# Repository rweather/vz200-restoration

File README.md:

VZ200 Restoration
=================

This repository chronicles my exploits in restoring a Dick Smith VZ200
that I got off eBay.  The VZ200 is a rebadged VTech Laser 200, which was
sold in Australia from 1983 onwards.

The eBay seller Ben had this to say about the unit: "It was an op-shop
pickup from my Nan and had been in storage in a plastic container for who
knows how long.  As it did not have any leads I never tested it."

## Technical specifications

* Z80A 8-bit CPU, running at 3.58MHz.
* 16K of ROM containing BASIC.
* 2K of video RAM for either 32 x 16 text mode or 128 x 64 graphics mode.
* 6K of user program RAM, expandable to 22K using a 16K RAM expansion module.
* 45 key chiclet keyboard organized in a 6x8 matrix.
* Motorola 6847 video processor.
* RF and composite video output.

Note: The VZ300 is essentially the same computer except that it has 16K of
user program RAM on-board and a mechanical keyboard.

Outside of Australia and New Zealand, the VZ200 and VZ300 were known as the
Laser 200 and Laser 310 respectively.

## Updates

Since doing the original restoration, I was gifted some more VZ200/VZ300
gear from a friend at work, Brian.  Brian got these years ago from an old
fellow in the local amateur radio network who was obviously a big fan of the
VZ computers, but was getting too old to work on them.

Many of the pieces have custom modifications and may or may not work.
Brian had 2 or 3 of everything.  He gave me these and kept the rest:

* Set of joysticks (working, just needed a clean).
* Printer interface.
* [16K memory expansion module that has been modified to 32K](Memory_Expansion_32K.md)
* Data casette recorder.
* Floppy disk controller and floppy disk drive.  Plus some floppy disks.
  Drive almost works but has a head crash; needs head re-alignment.
* Serial port kit.
* [Two VZ300's that were not working, but one now is.](VZ300_Restoration.md)

The links point at information about the restoration on each item.

Brian also gifted me a Microbee kit (assembled), two TRS-80 color computers,
and a TRS-80 printer/plotter.

I will gradually work on restoring these and post the results as I go.

And now onto the original restoration ...

## Restoration

Note: All images below have been scaled down.  Use "Open Image in New Tab"
or equivalent in your Web browser for a full-sized image.

### Initial condition of the unit

There were no power or video cables with the unit that was shipped to me.
The unit had not been powered on for a long time.  The power input is 9V DC
with a standard DC barrel jack, so power can be easily supplied with a
modern plugpack / wall wart.

The outside of the case was dirty, but nothing that some water, Windex,
paper towels, and elbow grease wouldn't fix.  The plastic was a little
yellowed but not too bad.

Serial number 075172.

The covers for the memory expansion and peripheral ports were still in place,
so I was hopeful that it had never been opened.

However, once inside I discovered some dirt and the braids connecting the
RF shield to ground had been cut:

It looks like someone had tried to remove the RF shield before and had
not succeeded.  The shield is soldered down to the motherboard, but some
of the legs were loose indicating partial success.

### Checking rail-to-rail resistance

I measured the resistance between 5V and ground - 284 ohms.  The same
between 9V and ground.  Probably OK.  Not a dead short anyway.

The resistance between 5V and 9V was 34 ohms, due to an actual 32 ohm
resistor between the two:

### Removing the keyboard

I had to remove the keyboard from the top half of the case to clean the
case properly.  It looks like the original keyboard was in a module that
was pushed in from the top and then snapped into place.  Removing the
screws was easy, but I couldn't slide out the keyboard PCB without
cutting the snaps or the cross-piece.  I elected to cut the cross-piece:

The keyboard PCB has scratched-on letters indicating which key is which.
That's useful.

After that, it was easy to remove the rubber membrane for cleaning.
The key caps themselves are molded into the membrane, so there are no
individual keys to get lost.  The membrane was filthy:

### Removing the RF shield

The person who tried to remove the RF shield didn't do a very good job.
Solder had bridged tracks, and one of the tracks was ripped right off the PCB:

Using a solder sucker, solder wick, flux, heat, and some patience,
I managed to clean up the excess solder and get the shield off:

Here is the same photo with the major components marked up:

And here is a diagram that shows the location of all IC's, looking forward
from the front of the PCB (not to scale):

### Cleaning the case and keyboard membrane

I cleaned the top and bottom of the case and the keyboard membrane
with Windex and water.  Some stubborn stains on the back were cleaned
off with isopropyl alchohol.

### First power on test

I connected a current-limited bench power supply set to 9V and 1A and
gingerly turned it on.  The 7805 voltage regulator was putting out 4.925V
and the system was consuming 650mA from the 9V supply.  So it looks like
no dead shorts on the board.

No blue smoke escaped, and the power LED turned on, so that's good.

### Checking signals

I checked the signals coming out of the CPU.  The clock on pin 6
was sitting at 3.57797MHz - close enough to 3.58MHz.

The address lines and most data lines had reasonable looking activity,
but D1, D2, and D6 had weird-looking signals like this for D6:

The base line of the signal is shifted up by about 1.7V.  D1 and D2 were
also shifted to half-way between 0V and 5V.  So there was a conflict
on the data bus somewhere.

### Video test

Connecting up a Composite-to-HDMI video converter, I got garbage on
the screen.  Powering on and off multiple times gives different garbage
each time:

The video clock into the MC6847 was around 3MHz, the "HS" horizontal sync
signal out was around 13kHz, and the "FS" frame sync signal out was 50Hz.

The video clock should be 3.58MHz.  However, the schematic gates the
main 3.58MHz system clock to generate the video clock.  "CLK" is the
main system clock:

In some parts of the frame during the horizontal and vertical sync times,
the video clock is disabled.  I think my oscilloscope was getting confused
and showing the average clock rate which undercounts due to the gating.
The same applies to the horizontal sync signal which isn't active for the
entire frame.

The frame sync was bang on 50Hz, and the generated video looked reasonable,
so the MC6847 must be getting the right timing.

The pictures don't show it, but there was a lot of static on the screen
which may be due to the clock signals, the CPU struggling to write to
video RAM, or a noisy component in the video output circuitry.

### Replacing the ROM's

From information I gleaned online, a common cause of bus crashes on the
VZ200 are the 2364 mask ROM's U9 and U10.  In [this video](https://www.youtube.com/watch?v=YIOjtE3j2aw)
from Tommy Ovesen at [Arctic Retro](https://www.arcticretro.com/),
he had similar screen corruption to my case.

Tommy replaced almost all the chips on the board before replacing the ROM's.
The ROM's were the ultimate culprit.  Rather than try replacing bus
transceivers, the CPU, or the video chip, I decided to learn from Tommy's
excellent work and start with the ROM's.

The wrinkle is that the original ROM's are 24-pin 2364's, but the best
replacements would be 28-pin 2764 EPROM's or (even better) AT28C64 EEPROM's.

It turns out that the PCB actually prefers 28-pin EPROM's!  There are
extra pin holes for the 28-pin footprint:

And on the back there are bodge wires to remap the 28-pin footprint into
24-pin so that the 2364's can be fitted:

If we look at the original schematic in the
[VZ200 Technical Reference Manual](http://www.vz200.org/bushy/VZ200_technical_reference_manual.pdf), we can see that the footprint was supposed to be 28-pin:

My guess is that the manufacturer originally intended to use 28-pin
2764 EPROM's, but to save cost they went with 24-pin 2364's instead.
Apparently it was cheaper to pay people to modify thousands of PCB's
with bodge wires than to re-spin the PCB.

This was good for me.  I removed the ROM's and the bodge wires, and then
re-bodged the PCB back to the 28-pin footprint for the two AT28C64B-15PU
EEPROM's that I purchased from Mouser.  The following table shows the pin
mapping between the 24-pin and 28-pin footprints, with the major changes
shown in bold:

<table border="1">
<tr><td><b>2364 Pin</b></td><td><b>Connection</b></td><td><b>AT28C64 Pin</b></td><td><b>Connection</b></td></tr>
<tr><td> </td><td> </td><td><b>1</b></td><td><b>5V</b></td></tr>
<tr><td> </td><td> </td><td><b>2</b></td><td><b>A12</b></td></tr>
<tr><td>1</td><td>A7</td><td>3</td><td>A7</td></tr>
<tr><td>2</td><td>A6</td><td>4</td><td>A6</td></tr>
<tr><td>3</td><td>A5</td><td>5</td><td>A5</td></tr>
<tr><td>4</td><td>A4</td><td>6</td><td>A4</td></tr>
<tr><td>5</td><td>A3</td><td>7</td><td>A3</td></tr>
<tr><td>6</td><td>A2</td><td>8</td><td>A2</td></tr>
<tr><td>7</td><td>A1</td><td>9</td><td>A1</td></tr>
<tr><td>8</td><td>A0</td><td>10</td><td>A0</td></tr>
<tr><td>9</td><td>D0</td><td>11</td><td>D0</td></tr>
<tr><td>10</td><td>D1</td><td>12</td><td>D1</td></tr>
<tr><td>11</td><td>D2</td><td>13</td><td>D2</td></tr>
<tr><td>12</td><td>GND</td><td>14</td><td>GND</td></tr>
<tr><td>13</td><td>D3</td><td>15</td><td>D3</td></tr>
<tr><td>14</td><td>D4</td><td>16</td><td>D4</td></tr>
<tr><td>15</td><td>D5</td><td>17</td><td>D5</td></tr>
<tr><td>16</td><td>D6</td><td>18</td><td>D6</td></tr>
<tr><td>17</td><td>D7</td><td>19</td><td>D7</td></tr>
<tr><td><b>18</b></td><td><b>A11</b></td><td><b>20</b></td><td><b>CE</b></td></tr>
<tr><td>19</td><td>A10</td><td>21</td><td>A10</td></tr>
<tr><td><b>20</b></td><td><b>CE</b></td><td><b>22</b></td><td><b>RD</b></td></tr>
<tr><td><b>21</b></td><td><b>A12</b></td><td><b>23</b></td><td><b>A11</b></td></tr>
<tr><td>22</td><td>A9</td><td>24</td><td>A9</td></tr>
<tr><td>23</td><td>A8</td><td>25</td><td>A8</td></tr>
<tr><td>24</td><td>5V</td><td>26</td><td>5V</td></tr>
<tr><td> </td><td> </td><td><b>27</b></td><td><b>5V</b></td></tr>
<tr><td> </td><td> </td><td><b>28</b></td><td><b>5V</b></td></tr>
</table>

<b>Note:</b> The chip enable "CE" pins for the two ROM's are connected
to different pins on U3 / 74LS139.  CE on U9 / ROM0 should be connected
to pin 4 on U3.  CE on U10 / ROM1 should be connected to pin 5 on U3.
All other pins are connected identically on both ROM's.

Here is the PCB with the new ROM's fitted:

And here are the bodge wires I added on the back of the PCB:

During the ROM removal process, I ripped up a few of the tracks so I have a
few more bodge wires than would be strictly necessary for the bold
alterations listed above.  Not my finest soldering job, but servicable.

The ROM images are available from Bushy's website.  Download the
"Everything" bundle from [here](http://www.vz200.org/bushy/software.html).
The ROM images are under "`ROMs/VZ ROM`" in the ZIP archive.  I used the files
`vtechv20.u09` and `vtechv20.u10`.

I used a TL866II Plus EEPROM Programmer and [minipro](https://gitlab.com/DavidGriffith/minipro) to flash the AT28C64B-15PU chips:

    <Put the first EEPROM in the programmer's socket>
    minipro -p AT28C64B -w vtechv20.u09

    <Put the second EEPROM in the programmer's socket>
    minipro -p AT28C64B -w vtechv20.u10

It is important to use the device name "AT28C64B" instead of "AT28C64"
with minipro.  The device name without the "B" didn't work.

With the 28-pin modifications above, it should be possible to fit
AT28C128 (16K) or AT28C256 (32K) instead of AT28C64 (8K).
The high address lines will be pulled high, so you will need to
flash the images into the top-most 8K of the replacement EEPROM's.
You will still need two EEPROM's, even if they are 16K or 32K in size,
because of how address decoding works on the PCB.

### Testing

After replacing the ROM's, I hooked up the power and composite video output
and turned the computer on.  This happened:

Yay!  It works!  The text is correct, the cursor blinks, and there is no
static on the screen.  So replacing the ROM's did the trick.

The current draw of the unit was originally 650mA on the 9V input.
After replacing the ROM's, the current draw is now 550mA.

### Keyboard ribbon cable

After repeated handling of the PCB while replacing the ROM's, the soldered-on
keyboard ribbon cable eventually tore off the PCB.  So I replaced it with a
proper connector setup using 2.54mm pin headers and sockets:

There is more than enough room in the case for the connector, so there
weren't any clearance issues:

After connecting the keyboard, I tried writing a little BASIC program:

All of the keys work reliably except CTRL.  Sometimes it works, but not always.
May be an alignment issue or something wrong with the membrane under the key.

### Fixing the CTRL key

I disassembled the keyboard again and carefully scrubbed the contacts on the
PCB and the membrane itself with dry cotton buds.  There was still a little
dirt in the membrane and on the contacts.

Previously I tightened the keyboard screws quite tight when I reassembled
the keyboard.  One theory I had was that the membrane didn't have enough
"play" because it was too tight / stretched around the CTRL key.
When I reassembled the keyboard I screwed in the screws until they
stopped moving.  But I didn't tighten any further than that.

Whether it was the cleaning or the untightened screws, the CTRL key now works.

### Conclusion

Here is a summary of the changes that I made:

* Clean the case and keyboard membrane.
* Remove the RF shield.
* Replace the 24-pin 2364 mask ROM's with 28-pin AT28C64B-15PU EEPROM's.
* Modify bodge wires around the ROM's to support the 28-pin footprint.
* Upgrade the ROM's to version 2.0.
* Remove the cross-piece in the case top to access the keyboard for cleaning.
* Replace the soldered keyboard ribbon cable with a proper connector.

Costings:

* USD$12 for the two replacement AT28C64B-15PU EEPROM's ($6 each).
* USD$2 for two 28-pin DIP sockets.
* USD$20 for a 9V DC plugpack / wall wart.
* Two weeks of nights and weekends for the full restoration.

And here it is in all of its restored glory:

## Schematics

I have reproduced the schematics from the VZ200 and VZ300 Technical
Reference Manuals in KiCad and generated PDF versions.  The original
schematics can be hard to read.

* [VZ200 Motherboard](schematics/VZ200/PDF/VZ200.pdf)
* [VZ300 Motherboard](schematics/VZ300/PDF/VZ300.pdf)
* [Printer Interface](schematics/VZ200_Printer_Interface/PDF/VZ200_Printer_Interface.pdf)
* [16K Memory Expansion Module](schematics/VZ200_16K_RAM_Expansion/PDF/VZ200_16K_RAM_Expansion.pdf)
* [Joystick Interface](schematics/VZ200_Joystick_Interface/PDF/VZ200_Joystick_Interface.pdf)

Note: The VZ200 motherboard schematic includes components for the PAL encoder
and 6K of Program RAM that were on separate PCB's in the original design.

There is a lot of missing detail in the manual.  Many of the components do
not have designators, so there is no way to know if a resistor was originally
R1, R63, or R128.  The PCB does not have a silkscreen marking the components.
In some cases, the component value is not provided.

For components without a designator, I made up numbers starting at 900;
e.g. R906, C912, U904, etc.  For components without a known value, I listed
the value as "???".  I was able to determine some of the values by inspecting
the actual PCB.

## Adapting the schematic

In theory the KiCad schematic could be modernised and then laid out on a
brand new PCB.  But a lot of work would be required to add footprints
and lay everything out.  Some of the components are pretty ancient
and would need modern replacements.

It would be nice to be able to build a brand new VZ200 from modern components.
I haven't attempted to do this, but others are welcome to try using my
schematic as a starting point.  Here is a list of things to fix:

* Replace the 6K of program RAM plus the 16K memory expansion module with a
single 32K static RAM chip on-board like the 62256.  Provide a switch for
6K operation for use with third-party expansion modules that provide
their own RAM.
* The 2K of video memory is on a separate data and address bus,
so it will probably need special handling.
* To avoid screen flicker, double the main system clock from 3.58MHz to
7.16MHz and use alternating clock pulses for the CPU and MC6847 to avoid
bus contention.
* Replace the two 8K mask ROM's with a modern 16K or 32K EEPROM.
* The MC6847 Video Display Generator (VDG) has additional graphics modes
that were not accessible with the original design.  Some people have
already modified their VZ200's to access these modes.
* The chiclet keyboard is horrible, but a lot of software depends upon
the specific arrangement of buttons in the key matrix.  Consider replacing
with mechanical key switches like on the VZ300, but the same matrix
arrangement.
* As an alternative keyboard approach, use a microcontroller to convert the
signals from a standard USB keyboard into the key matrix signals.
* If you have FPGA skills, then consider replacing the MC6847 with an
alternative that puts out standard RGB or HDMI video instead of
composite video.  This would greatly simplify the video output circuitry.
* The original schematic in the technical reference manual did not have
100nF filter capacitors on the major chips.  The actual PCB does have a
small number of 40nF capacitors and some electrolytics scattered around
that were not listed in the original schematic.  I have captured some of
them in my schematic.  Ensure that the voltage rails are properly filtered.
* U13 is a 74LS04 hex inverter with a spare inverter gate, but the input
was not tied to ground or 5V.  There is also a spare XOR gate in the
16K memory expansion module whose inputs aren't tied high or low either.

## Other documentation

* [VZ200 startup sequence](doc/startup-sequence.md)
* [Useful Memory Locations](doc/useful-locations.md)

## Resources

* [Wikipedia article](https://en.wikipedia.org/wiki/VTech_Laser_200)
* [vz200.org](http://vz200.org/)
* [Bushy's VZ200 website](http://www.vz200.org/bushy/)
* [VZ200 Technical Reference Manual](http://www.vz200.org/bushy/VZ200_technical_reference_manual.pdf) from Bushy's website.
* [VZ300 Technical Reference Manual](http://www.vz200.org/bushy/VZ300_tech_manual.pdf) from Bushy's website.

## Acknowledgements

I was inspired to try my hand at restoring a vintage 1980's computer by the
following YouTubers:

* [Adrian's Digital Basement](https://www.youtube.com/@adriansdigitalbasement)
* [Artic Retro](https://www.youtube.com/@Arcticretro)
* [Noel's Retro Lab](https://www.youtube.com/@NoelsRetroLab)
* [The 8-Bit Guy](https://www.youtube.com/@The8BitGuy)
* [Usagi Electric](https://www.youtube.com/@UsagiElectric)

Artic Retro in particular is an expert in VZ200 / Laser 200 computers.

Thanks for sharing the enthusiam and teaching me so much!

## History

My first computer was a Dick Smith Cat, which was a rebadged Laser 3000.
Mine died a long time ago and I sent it to the dump.  I now wish I hadn't!

I thought that the VZ200 I found on eBay would be the closest I would
ever come to my beloved Cat - it is a similar vintage.  However as of
July 2024, I now have a Cat again after purchasing one on Gumtree.  Yay!

I am also looking for the following to complete my set of early 1980's
Australian computers.  Some of which I have since found:

* Dick Smith Sorcerer (found May 2024)
* Dick Smith System 80 (TRS-80 clone) (found January 2025)
* Dick Smith Super 80 (this was a kit made in concert with Electronics Australia)
* Microbee (found Jan 2024)
* Electronics Australia or ETI kit computers like DREAM-6800, ETI-660, or EDUC-8

Other restoration information of mine on github:

* [Kit Microbee](https://github.com/rweather/microbee-restoration)
* [Dick Smith Cat](https://github.com/rweather/cat-technical-information)
* [Dick Smith System 80](https://github.com/rweather/system80-restoration)

## License

<p xmlns:cc="http://creativecommons.org/ns#" xmlns:dct="http://purl.org/dc/terms/"><span property="dct:title">VZ200 Restoration</span> by <span property="cc:attributionName">Rhys Weatherley</span> is licensed under <a href="http://creativecommons.org/licenses/by-nc-sa/4.0/?ref=chooser-v1" target="_blank" rel="license noopener noreferrer" style="display:inline-block;">Attribution-NonCommercial-ShareAlike 4.0 International</a></p>

## Contact

For more information on this project, to report bugs, or to suggest
improvements, please contact the author Rhys Weatherley via
[email](mailto:rhys.weatherley@gmail.com).

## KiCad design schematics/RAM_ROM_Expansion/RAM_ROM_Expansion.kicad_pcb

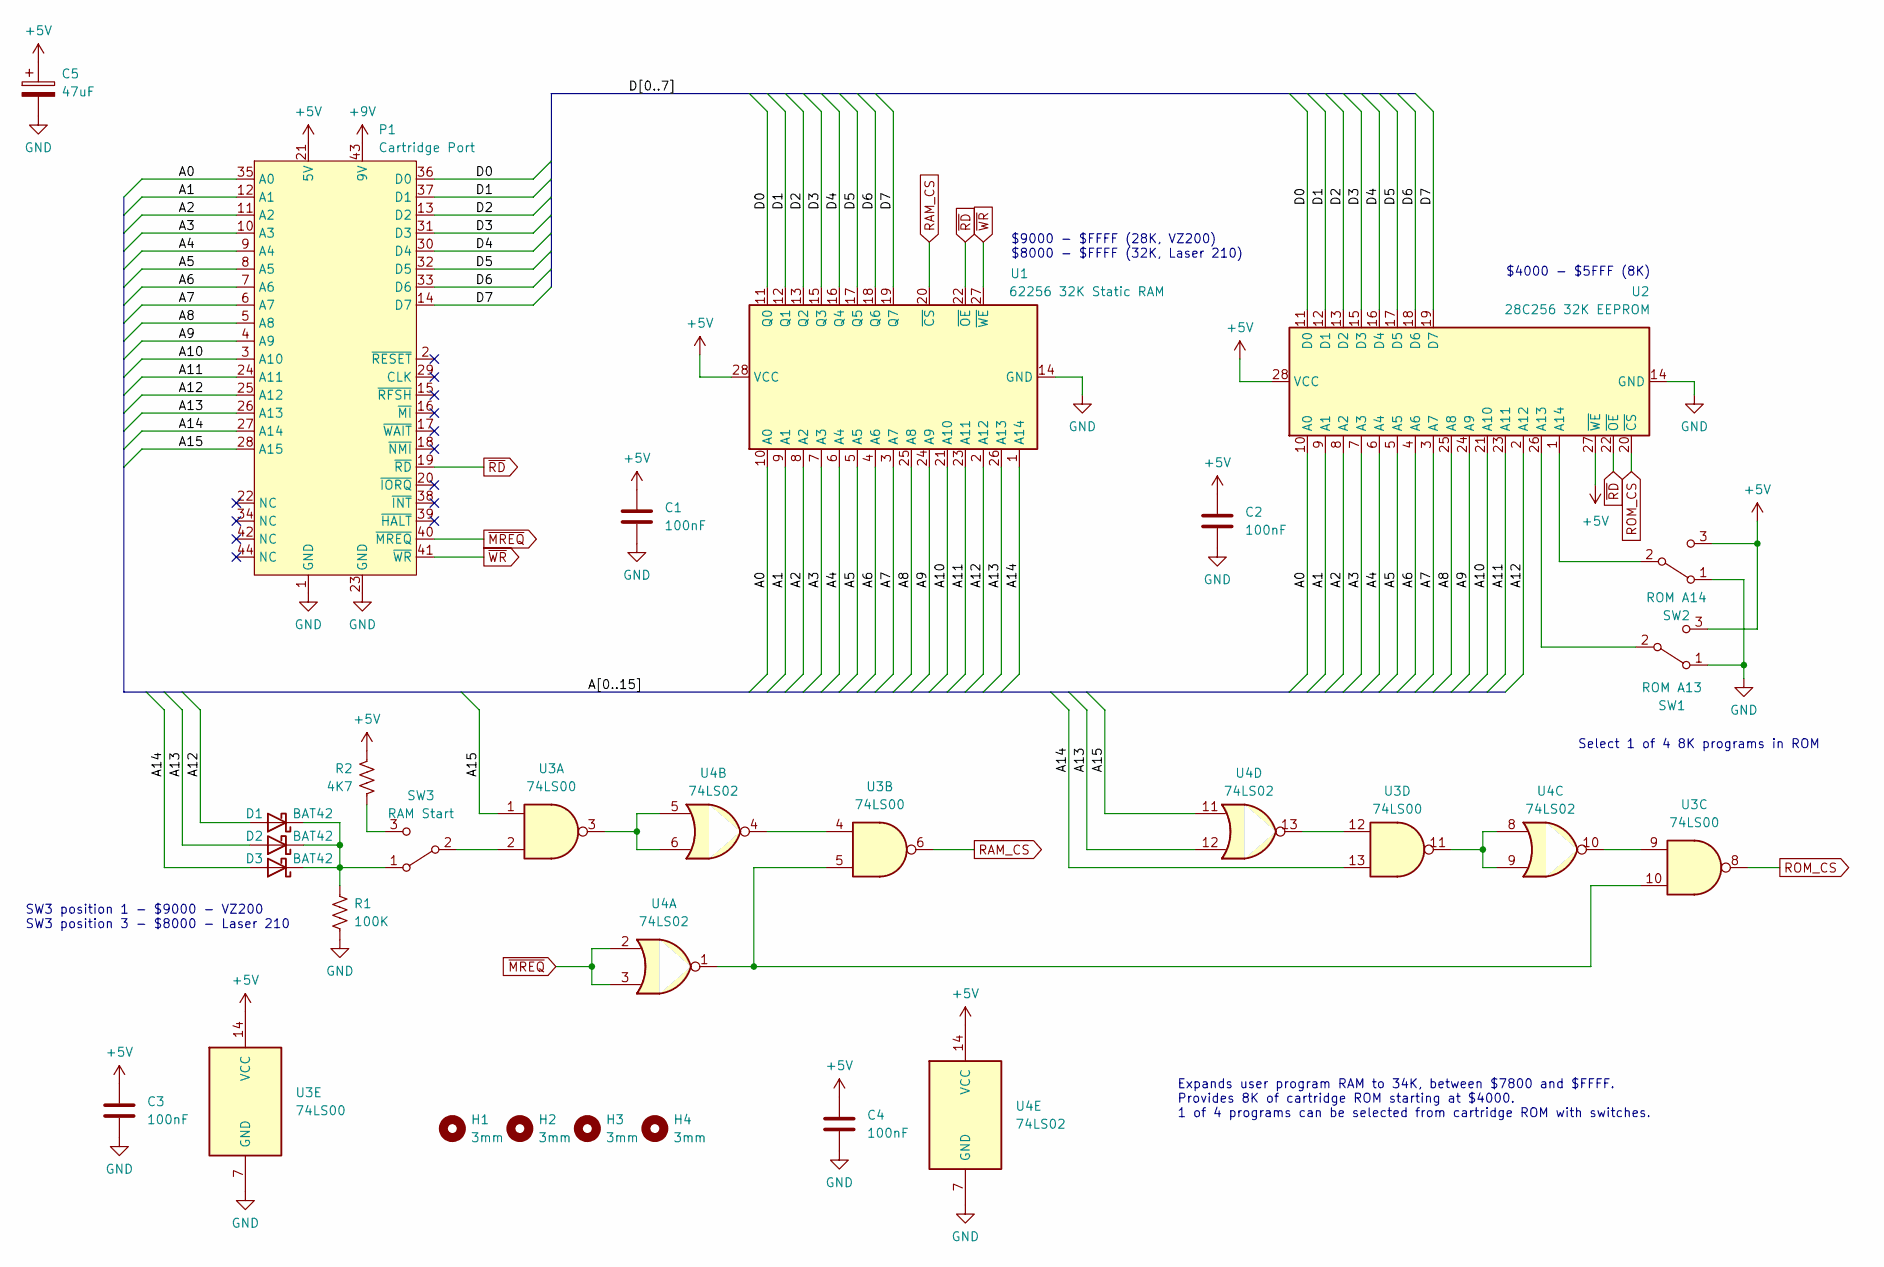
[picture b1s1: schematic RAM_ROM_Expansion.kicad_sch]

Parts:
C1, C2, C3, C4: 100nF; C_Disc_D5.0mm_W2.5mm_P5.00mm
C5: 47uF; CP_Radial_D6.3mm_P2.50mm
D1, D2, D3: BAT42; D_DO-35_SOD27_P7.62mm_Horizontal
H1, H2, H3, H4: 3mm; MountingHole_3mm
P1: Cartridge Port; VZ200_Cartridge_Port
R1: 100K; R_Axial_DIN0207_L6.3mm_D2.5mm_P7.62mm_Horizontal
R2: 4K7; R_Axial_DIN0207_L6.3mm_D2.5mm_P7.62mm_Horizontal
SW1: ROM A13; PinHeader_1x03_P2.54mm_Vertical
SW2: ROM A14; PinHeader_1x03_P2.54mm_Vertical
SW3: RAM Start; PinHeader_1x03_P2.54mm_Vertical
U1: 62256 32K Static RAM; DIP-28_W15.24mm_Socket
U2: 28C256 32K EEPROM; DIP-28_W15.24mm_Socket
U3: 74LS00; DIP-14_W7.62mm_Socket
U4: 74LS02; DIP-14_W7.62mm_Socket

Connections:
+5V: C1.1, C2.1, C3.1, C4.1, C5.1, P1.21 (5V), R2.1, SW1.3 (C), SW2.3 (C), U1.28 (VCC), U2.27 (~WE), U2.28 (VCC), U3.14 (VCC), U4.14 (VCC)
+9V: P1.43 (9V)
/A0: P1.35 (A0), U1.10 (A0), U2.10 (A0)
/A1: P1.12 (A1), U1.9 (A1), U2.9 (A1)
/A2: P1.11 (A2), U1.8 (A2), U2.8 (A2)
/A3: P1.10 (A3), U1.7 (A3), U2.7 (A3)
/A4: P1.9 (A4), U1.6 (A4), U2.6 (A4)
/A5: P1.8 (A5), U1.5 (A5), U2.5 (A5)
/A6: P1.7 (A6), U1.4 (A6), U2.4 (A6)
/A7: P1.6 (A7), U1.3 (A7), U2.3 (A7)
/A8: P1.5 (A8), U1.25 (A8), U2.25 (A8)
/A9: P1.4 (A9), U1.24 (A9), U2.24 (A9)
/A10: P1.3 (A10), U1.21 (A10), U2.21 (A10)
/A11: P1.24 (A11), U1.23 (A11), U2.23 (A11)
/A12: D1.2 (A), P1.25 (A12), U1.2 (A12), U2.2 (A12)
/A13: D2.2 (A), P1.26 (A13), U1.26 (A13), U4.12
/A14: D3.2 (A), P1.27 (A14), U1.1 (A14), U3.13
/A15: P1.28 (A15), U3.1, U4.11
/D0: P1.36 (D0), U1.11 (Q0), U2.11 (D0)
/D1: P1.37 (D1), U1.12 (Q1), U2.12 (D1)
/D2: P1.13 (D2), U1.13 (Q2), U2.13 (D2)
/D3: P1.31 (D3), U1.15 (Q3), U2.15 (D3)
/D4: P1.30 (D4), U1.16 (Q4), U2.16 (D4)
/D5: P1.32 (D5), U1.17 (Q5), U2.17 (D5)
/D6: P1.33 (D6), U1.18 (Q6), U2.18 (D6)
/D7: P1.14 (D7), U1.19 (Q7), U2.19 (D7)
GND: C1.2, C2.2, C3.2, C4.2, C5.2, P1.1 (GND), P1.23 (GND), R1.2, SW1.1 (A), SW2.1 (A), U1.14 (GND), U2.14 (GND), U3.7 (GND), U4.7 (GND)
unnamed: D1.1 (K), D2.1 (K), D3.1 (K), R1.1, SW3.1 (A)
unnamed: SW1.2 (B), U2.26 (A13)
unnamed: SW2.2 (B), U2.1 (A14)
unnamed: SW3.2 (B), U3.2
unnamed: R2.2, SW3.3 (C)
unnamed: U3.3, U4.5, U4.6
unnamed: U3.4, U4.4
unnamed: U3.9, U4.10
unnamed: U3.5, U3.10, U4.1
unnamed: U3.11, U4.8, U4.9
unnamed: U3.12, U4.13
RAM_CS: U1.20 (~CS), U3.6
ROM_CS: U2.20 (~CS), U3.8
~MREQ: P1.40 (~MREQ), U4.2, U4.3
~RD: P1.19 (~RD), U1.22 (~OE), U2.22 (~OE)
~WR: P1.41 (~WR), U1.27 (~WE)

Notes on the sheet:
Expands user program RAM to 34K, between $7800 and $FFFF. Provides 8K of cartridge ROM starting at $4000. 1 of 4 programs can be selected from cartridge ROM with switches.
Select 1 of 4 8K programs in ROM
$4000 - $5FFF (8K)
SW3 position 1 - $9000 - VZ200 SW3 position 3 - $8000 - Laser 210
$9000 - $FFFF (28K, VZ200) $8000 - $FFFF (32K, Laser 210)

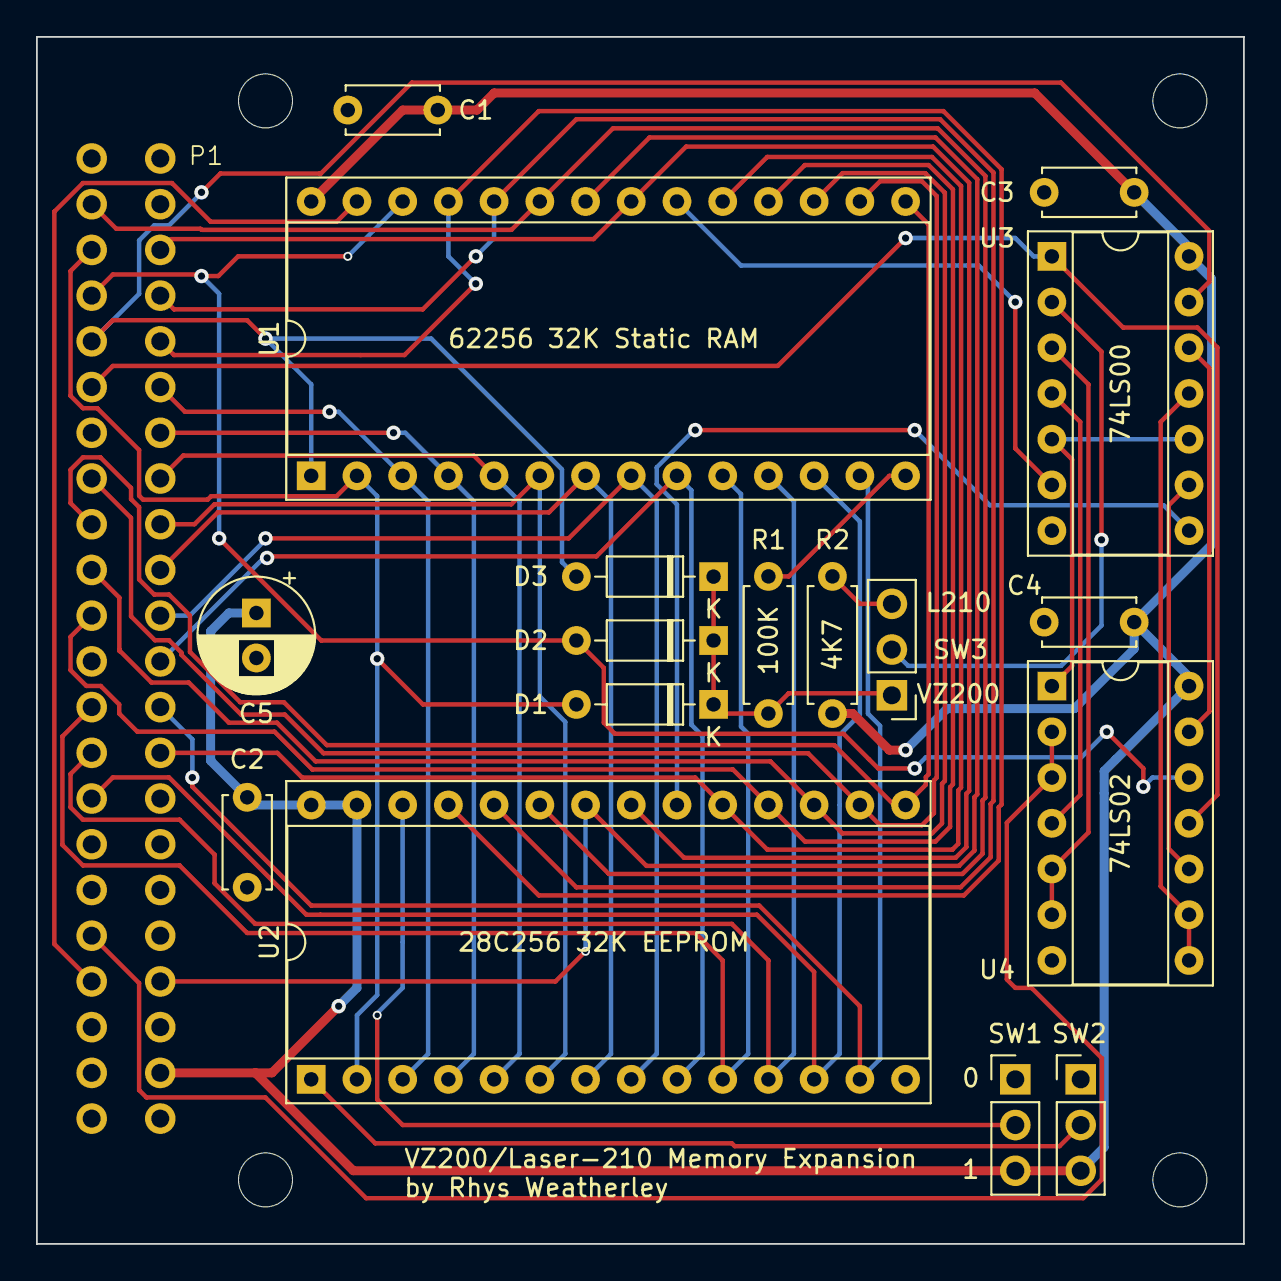
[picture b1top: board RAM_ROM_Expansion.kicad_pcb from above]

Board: 2 copper layers, 67.1 x 67.1 mm, 22 parts (0 on the bottom side), 42 nets.

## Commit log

2023-12-29 Recreate the VZ200 schematic in Kicad
2023-12-29 Schematic for the VZ200 printer interface
2023-12-29 16K Memory Expansion Cartridge for VZ200
2023-12-29 Mention that the 6K of Program RAM is on a separate PCB
2023-12-30 More documentation and license
2023-12-31 Custom RAM/ROM expansion board concept
2023-12-31 Add title and revision details to the schematic sheets
2024-01-01 Disassembler for .VZ and ROM files
2024-01-02 Documentation
2024-01-03 Decoding more internal addresses in the BASIC ROM's
2024-01-05 Restoration Part 1
2024-01-05 Update motherboard schematic based on inspection of the actual board
2024-01-17 Restoration Part 2
2024-01-17 Markdown fixes for github
2024-01-19 List of other computers I'm looking for
2024-01-19 Fix the CTRL key
2024-01-20 Disassemble machine code programs with a BASIC execution stub
2024-01-23 VZ200/VZ300 Joystick Interface Schematic
2024-01-24 Update part numbers for the joystick interface
2024-01-24 Updates on recently acquired gear
2024-01-25 D.Newcombe's Custom 32K RAM Expansion Module
2024-01-28 Recognise another type of magic header for VZ files
2024-01-28 Convert .BAS files into .VZ
2024-01-28 Better handling for special characters in BASIC strings
2024-02-16 VZ300 restoration
2024-04-01 Updates on peripherals
2024-04-04 Handle signed IX/IY displacements in vzdasm
2024-04-05 Fix opcodes for "push ix" and "push iy"
2024-04-30 VZ300 schematic in KiCad
2024-04-30 Fix some minor issues in the VZ300 schematic
2024-05-12 VZ300 non-working unit restoration, part 1
2024-05-15 Dead Test ROM
2024-05-15 Document the placement of DRAM chips in the VZ300 schematic
2025-01-12 Update the list of Australian computers with those I have found
2025-02-03 Fix a bug in the dead test on devices with 34K of RAM
2025-02-03 Make VRAM failure more obvious in the dead test
